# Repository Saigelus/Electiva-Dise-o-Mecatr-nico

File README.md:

Link a video de ESP32 con Antena!: https://youtu.be/J3MrhWr3mPE

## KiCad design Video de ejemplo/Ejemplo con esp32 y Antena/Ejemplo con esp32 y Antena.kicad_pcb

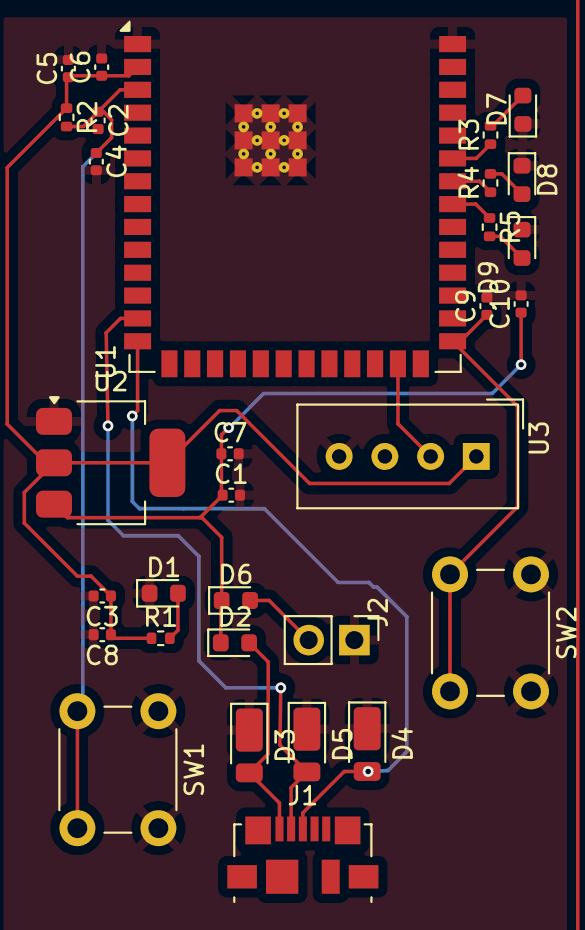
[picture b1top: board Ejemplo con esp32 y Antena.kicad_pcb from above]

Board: 2 copper layers, 31 parts (0 on the bottom side), 17 nets.

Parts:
C1, C3, C5, C10: 10uF; C_0402_1005Metric
C2: 1uF; C_0402_1005Metric
C4, C6, C7, C8, C9: 0.1uF; C_0402_1005Metric
D1: LED; LED_0603_1608Metric
D2, D6: D; D_0603_1608Metric
D3, D4, D5: D_TVS; D_PowerDI-123
D7: LED_3; LED_0603_1608Metric
D8: LED_2; LED_0603_1608Metric
D9: LED_1; LED_0603_1608Metric
J1: USB_OTG; USB_Micro-B_Molex_47346-0001
J2: Conn_01x02_Pin; PinHeader_1x02_P2.54mm_Vertical
R1: 1k; R_0402_1005Metric
R2: 10k; R_0402_1005Metric
R3, R4, R5: 220; R_0402_1005Metric
SW1: RST; SW_PUSH_6mm_H5mm
SW2: Boot; SW_PUSH_6mm_H5mm
U1: ESP32-S3-WROOM-1; ESP32-S3-WROOM-2
U2: AMS1117; SOT-223-3_TabPin2
U3: DHT11; Aosong_DHT11_5.5x12.0_P2.54mm

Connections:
EN: C2.1, C4.1, R2.2, SW1.2, U1.3 (EN)
Earth: C1.2, C2.2, C3.2, C4.2, C5.2, C6.2, C7.2, C8.2, C9.2, C10.2, D1.1 (K), D3.1 (A1), D4.1 (A1), D5.1 (A1), D7.1 (K), D8.1 (K), D9.1 (K), J1.5 (GND), J2.1, SW1.1, SW2.1, U1.1 (GND), U1.40 (GND), U1.41 (GND), U2.1 (ADJ), U3.4 (GND)
GPIO0: C9.1, SW2.2, U1.27 (IO0)
GPIO19: D5.2 (A2), J1.2 (D-), U1.13 (IO19)
GPIO20: D4.2 (A2), J1.3 (D+), U1.14 (IO20)
unnamed: D1.2 (A), R1.2
unnamed: D2.2 (A), D3.2 (A2), J1.1 (VBUS)
unnamed: D6.2 (A), J2.2
unnamed: D7.2 (A), R3.2
unnamed: D8.2 (A), R4.2
unnamed: D9.2 (A), R5.2
unnamed: R5.1, U1.33 (IO40)
unnamed: R4.1, U1.34 (IO41)
unnamed: R3.1, U1.35 (IO42)
unnamed: U1.25 (IO48), U3.2 (DATA)
V_in: C3.1, C5.1, C6.1, C8.1, R1.1, R2.1, U1.2 (3V3), U2.2 (VO), U3.1 (VDD)
V_in_ext: C1.1, C7.1, C10.1, D2.1 (K), D6.1 (K), U2.3 (VI)

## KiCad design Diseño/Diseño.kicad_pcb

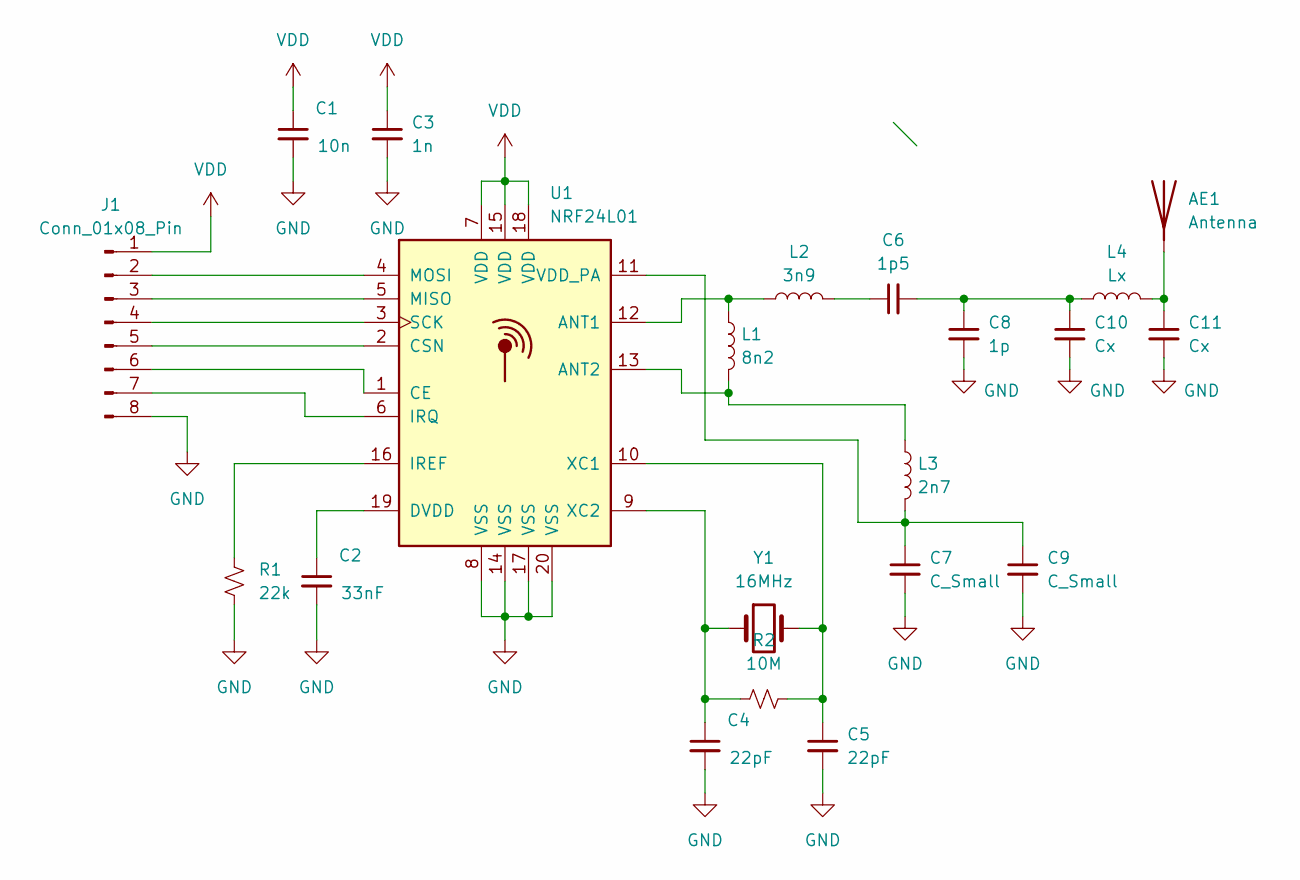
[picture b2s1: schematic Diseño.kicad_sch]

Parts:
AE1: Antenna; Texas_SWRA117D_2.4GHz_Right
C1: 10n; C_0402_1005Metric
C2: 33nF; C_0402_1005Metric
C3: 1n; C_0402_1005Metric
C4, C5: 22pF; C_0402_1005Metric
C6: 1p5; C_0402_1005Metric
C7, C9: C_Small; C_0402_1005Metric
C8: 1p; C_0402_1005Metric
C10, C11: Cx; C_0402_1005Metric
J1: Conn_01x08_Pin; Hirose_DF13-08P-1.25DS_1x08_P1.25mm_Horizontal
L1: 8n2; L_0402_1005Metric
L2: 3n9; L_0402_1005Metric
L3: 2n7; L_0402_1005Metric
L4: Lx; L_0402_1005Metric
R1: 22k; R_0402_1005Metric
R2: 10M; R_0402_1005Metric
U1: NRF24L01; QFN-20-1EP_4x4mm_P0.5mm_EP2.5x2.5mm
Y1: 16MHz; Crystal_SMD_3215-2Pin_3.2x1.5mm

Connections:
GND: C1.2, C2.2, C3.2, C4.2, C5.2, C7.2, C8.2, C9.2, C10.2, C11.2, J1.8, R1.1, U1.8 (VSS), U1.14 (VSS), U1.17 (VSS), U1.20 (VSS)
unnamed: AE1.1 (A), C11.1, L4.2
unnamed: C6.1, L2.2
unnamed: C6.2, C8.1, C10.1, L4.1
unnamed: J1.2, U1.4 (MOSI)
unnamed: J1.3, U1.5 (MISO)
unnamed: J1.4, U1.3 (SCK)
unnamed: J1.5, U1.2 (CSN)
unnamed: J1.6, U1.1 (CE)
unnamed: J1.7, U1.6 (IRQ)
unnamed: L1.1, L2.1, U1.12 (ANT1)
unnamed: L1.2, L3.1, U1.13 (ANT2)
unnamed: C2.1, U1.19 (DVDD)
unnamed: R1.2, U1.16 (IREF)
unnamed: C7.1, C9.1, L3.2, U1.11 (VDD_PA)
unnamed: C5.1, R2.2, U1.10 (XC1), Y1.2
unnamed: C4.1, R2.1, U1.9 (XC2), Y1.1
VDD: C1.1, C3.1, J1.1, U1.7 (VDD), U1.15 (VDD), U1.18 (VDD)

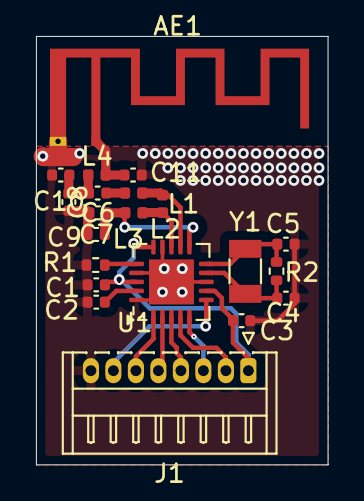
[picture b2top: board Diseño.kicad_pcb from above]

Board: 2 copper layers, 16.2 x 23.8 mm, 21 parts (0 on the bottom side), 18 nets.

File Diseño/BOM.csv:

"Reference","Value","Datasheet","Footprint","Qty","DNP"
"AE1","Antenna","~","","1",""
"C1","10n","~","Capacitor_SMD:C_0402_1005Metric","1",""
"C2","33nF","~","Capacitor_SMD:C_0402_1005Metric","1",""
"C3","1n","~","Capacitor_SMD:C_0402_1005Metric","1",""
"C4,C5","22pF","~","Capacitor_SMD:C_0402_1005Metric","2",""
"C6","1p5","~","Capacitor_SMD:C_0402_1005Metric","1",""
"C7,C9","C_Small","~","Capacitor_SMD:C_0402_1005Metric","2",""
"C8","1p","~","Capacitor_SMD:C_0402_1005Metric","1",""
"C10,C11","Cx","~","Capacitor_SMD:C_0402_1005Metric","2",""
"J1","Conn_01x08_Pin","~","Connector_Hirose:Hirose_DF13-08P-1.25DS_1x08_P1.25mm_Horizontal","1",""
"L1","8n2","~","Inductor_SMD:L_0402_1005Metric","1",""
"L2,L4","3n9","~","Inductor_SMD:L_0402_1005Metric","2",""
"L3","2n7","~","Inductor_SMD:L_0402_1005Metric","1",""
"R1","22k","~","","1",""
"R2","10M","~","","1",""
"U1","NRF24L01","http://www.nordicsemi.com/eng/content/download/2730/34105/fi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","Package_DFN_QFN:QFN-20-1EP_4x4mm_P0.5mm_EP2.5x2.5mm","1",""
"Y1","16MHz","~","Crystal:Crystal_SMD_3215-2Pin_3.2x1.5mm","1",""
